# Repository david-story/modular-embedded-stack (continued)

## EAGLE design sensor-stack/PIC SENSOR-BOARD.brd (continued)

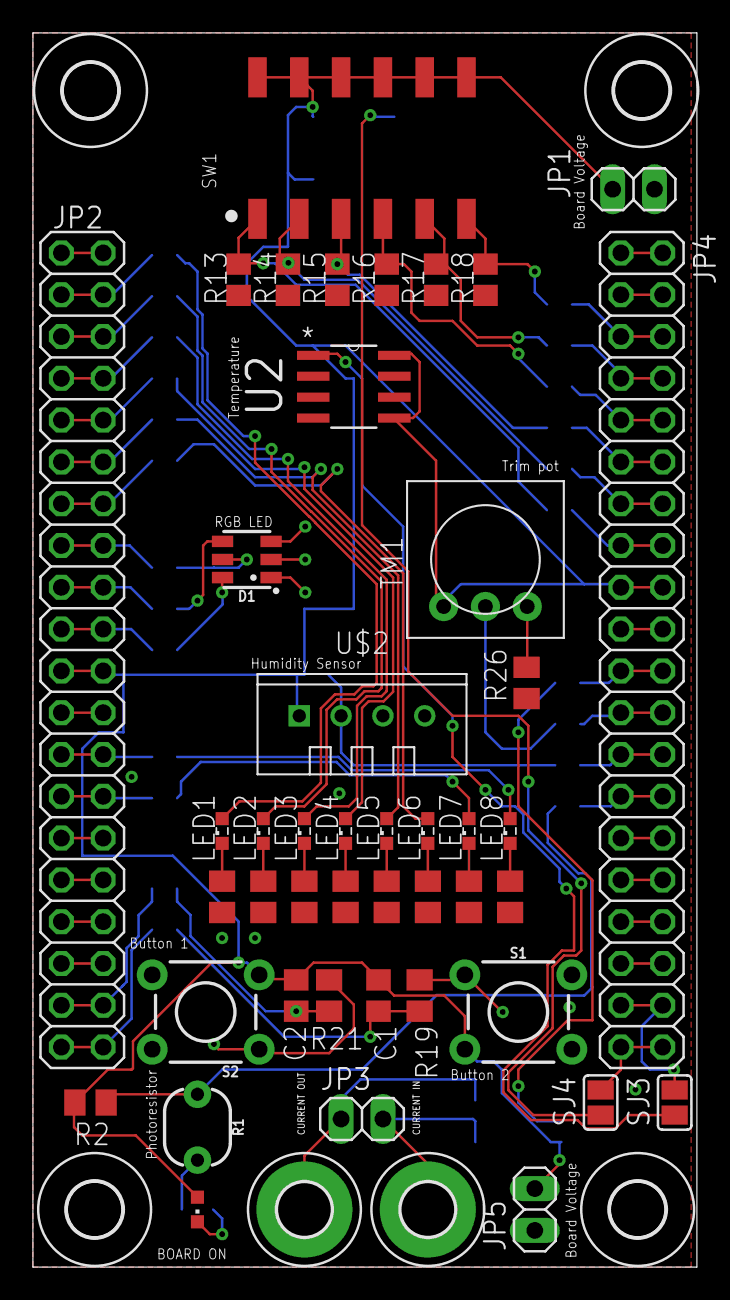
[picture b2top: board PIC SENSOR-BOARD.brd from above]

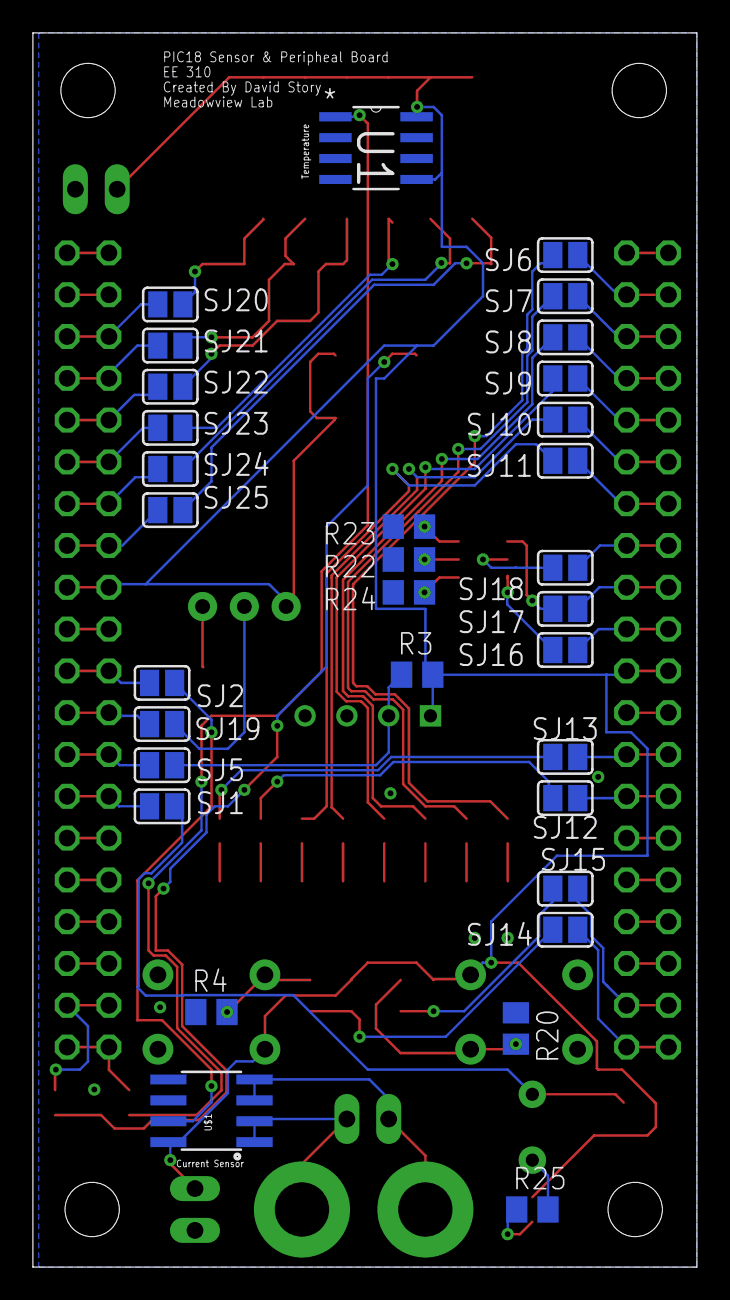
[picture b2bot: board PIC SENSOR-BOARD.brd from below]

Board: 2 copper layers, 40.4 x 75.0 mm, 82 parts (32 on the bottom side), 80 nets.

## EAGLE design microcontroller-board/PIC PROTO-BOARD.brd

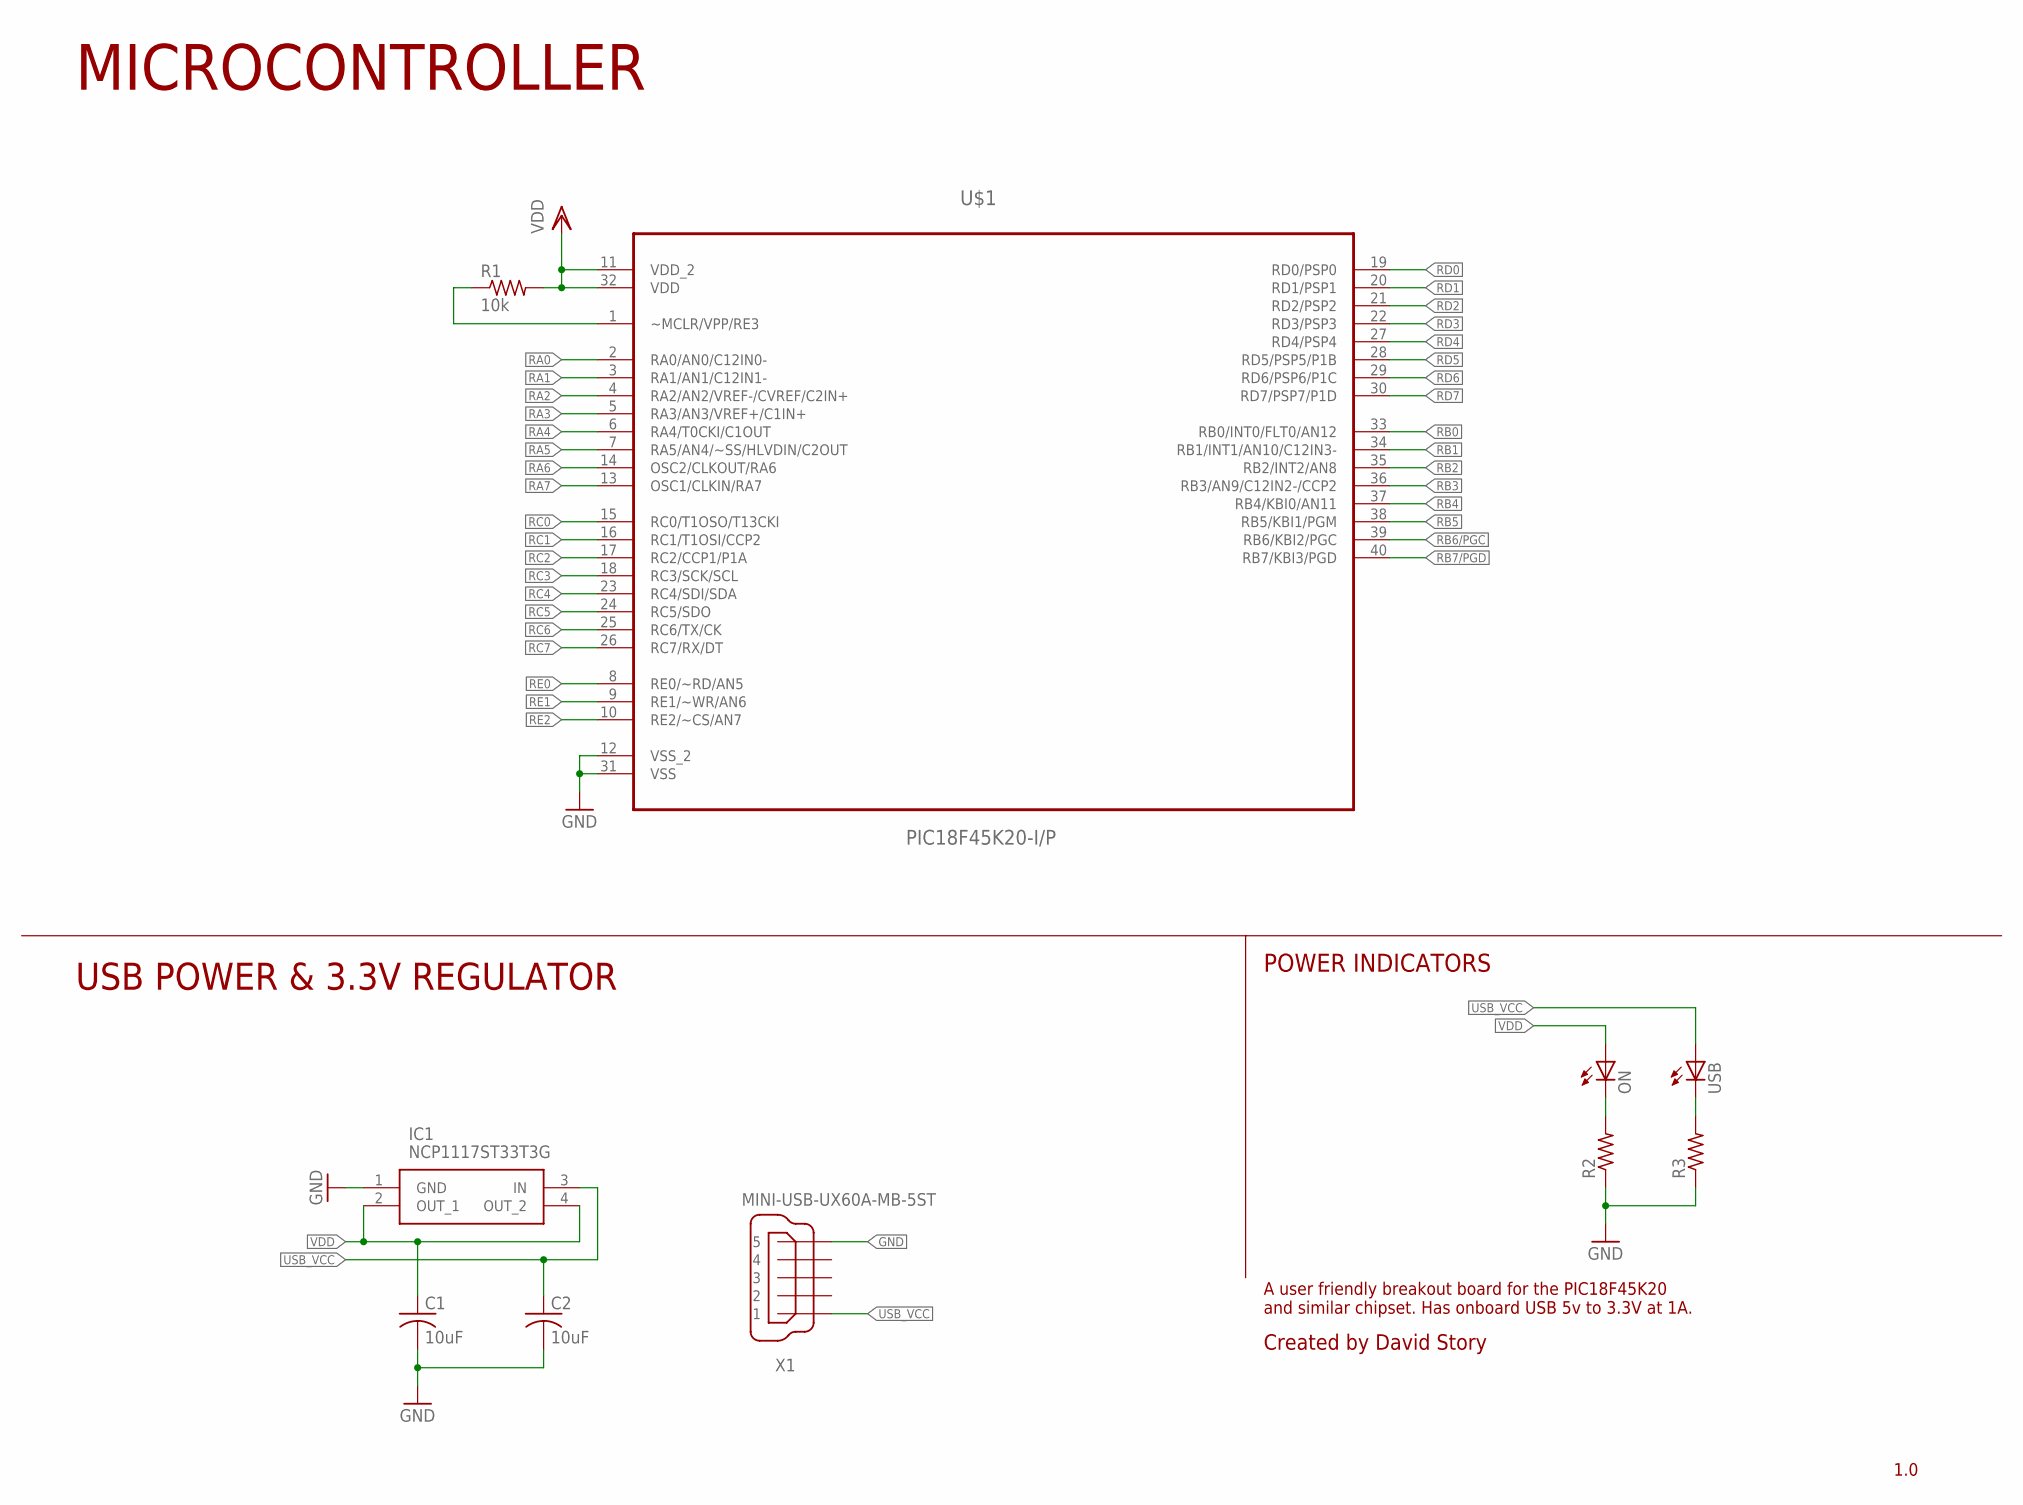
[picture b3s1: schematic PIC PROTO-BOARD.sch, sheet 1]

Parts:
C1, C2: 10uF; C0805
IC1: NCP1117ST33T3G; SOT230P700X180-4N
ON: LEDCHIP-LED0603; CHIP-LED0603
R1: 10k; R0805
R2, R3: R-US_R0603; R0603
U$1: PIC18F45K20-I/P; DIP254P1524X635-40
USB: LEDCHIP-LED0603; CHIP-LED0603
X1: MINI-USB-UX60A-MB-5ST; UX60A-MB-5ST

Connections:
GND: C1.2, C2.2, IC1.1 (GND), R2.1, R3.1, U$1.12 (VSS_2), U$1.31 (VSS), X1.5; also elsewhere on the board
MCLR: R1.1, U$1.1 (~MCLR/VPP/RE3); also elsewhere on the board
ON_CATHODE: ON.C, R2.2
RA0: U$1.2 (RA0/AN0/C12IN0-); also elsewhere on the board
RA1: U$1.3 (RA1/AN1/C12IN1-); also elsewhere on the board
RA2: U$1.4 (RA2/AN2/VREF-/CVREF/C2IN+); also elsewhere on the board
RA3: U$1.5 (RA3/AN3/VREF+/C1IN+); also elsewhere on the board
RA4: U$1.6 (RA4/T0CKI/C1OUT); also elsewhere on the board
RA5: U$1.7 (RA5/AN4/~SS/HLVDIN/C2OUT); also elsewhere on the board
RA6: U$1.14 (OSC2/CLKOUT/RA6); also elsewhere on the board
RA7: U$1.13 (OSC1/CLKIN/RA7); also elsewhere on the board
RB0: U$1.33 (RB0/INT0/FLT0/AN12); also elsewhere on the board
RB1: U$1.34 (RB1/INT1/AN10/C12IN3-); also elsewhere on the board
RB2: U$1.35 (RB2/INT2/AN8); also elsewhere on the board
RB3: U$1.36 (RB3/AN9/C12IN2-/CCP2); also elsewhere on the board
RB4: U$1.37 (RB4/KBI0/AN11); also elsewhere on the board
RB5: U$1.38 (RB5/KBI1/PGM); also elsewhere on the board
RB6/PGC: U$1.39 (RB6/KBI2/PGC); also elsewhere on the board
RB7/PGD: U$1.40 (RB7/KBI3/PGD); also elsewhere on the board
RC0: U$1.15 (RC0/T1OSO/T13CKI); also elsewhere on the board
RC1: U$1.16 (RC1/T1OSI/CCP2); also elsewhere on the board
RC2: U$1.17 (RC2/CCP1/P1A); also elsewhere on the board
RC3: U$1.18 (RC3/SCK/SCL); also elsewhere on the board
RC4: U$1.23 (RC4/SDI/SDA); also elsewhere on the board
RC5: U$1.24 (RC5/SDO); also elsewhere on the board
RC6: U$1.25 (RC6/TX/CK); also elsewhere on the board
RC7: U$1.26 (RC7/RX/DT); also elsewhere on the board
RD0: U$1.19 (RD0/PSP0); also elsewhere on the board
RD1: U$1.20 (RD1/PSP1); also elsewhere on the board
RD2: U$1.21 (RD2/PSP2); also elsewhere on the board
RD3: U$1.22 (RD3/PSP3); also elsewhere on the board
RD4: U$1.27 (RD4/PSP4); also elsewhere on the board
RD5: U$1.28 (RD5/PSP5/P1B); also elsewhere on the board
RD6: U$1.29 (RD6/PSP6/P1C); also elsewhere on the board
RD7: U$1.30 (RD7/PSP7/P1D); also elsewhere on the board
RE0: U$1.8 (RE0/~RD/AN5); also elsewhere on the board
RE1: U$1.9 (RE1/~WR/AN6); also elsewhere on the board
RE2: U$1.10 (RE2/~CS/AN7); also elsewhere on the board
USB_CATHODE: R3.2, USB.C
USB_VCC: C2.1, IC1.3 (IN), USB.A, X1.1
VDD: C1.1, IC1.2 (OUT_1), IC1.4 (OUT_2), ON.A, R1.2, U$1.11 (VDD_2), U$1.32 (VDD); also elsewhere on the board

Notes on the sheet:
Created by David Story
1.0
MICROCONTROLLER
USB POWER & 3.3V REGULATOR
POWER INDICATORS
A user friendly breakout board for the PIC18F45K20 and similar chipset. Has onboard USB 5v to 3.3V at 1A.

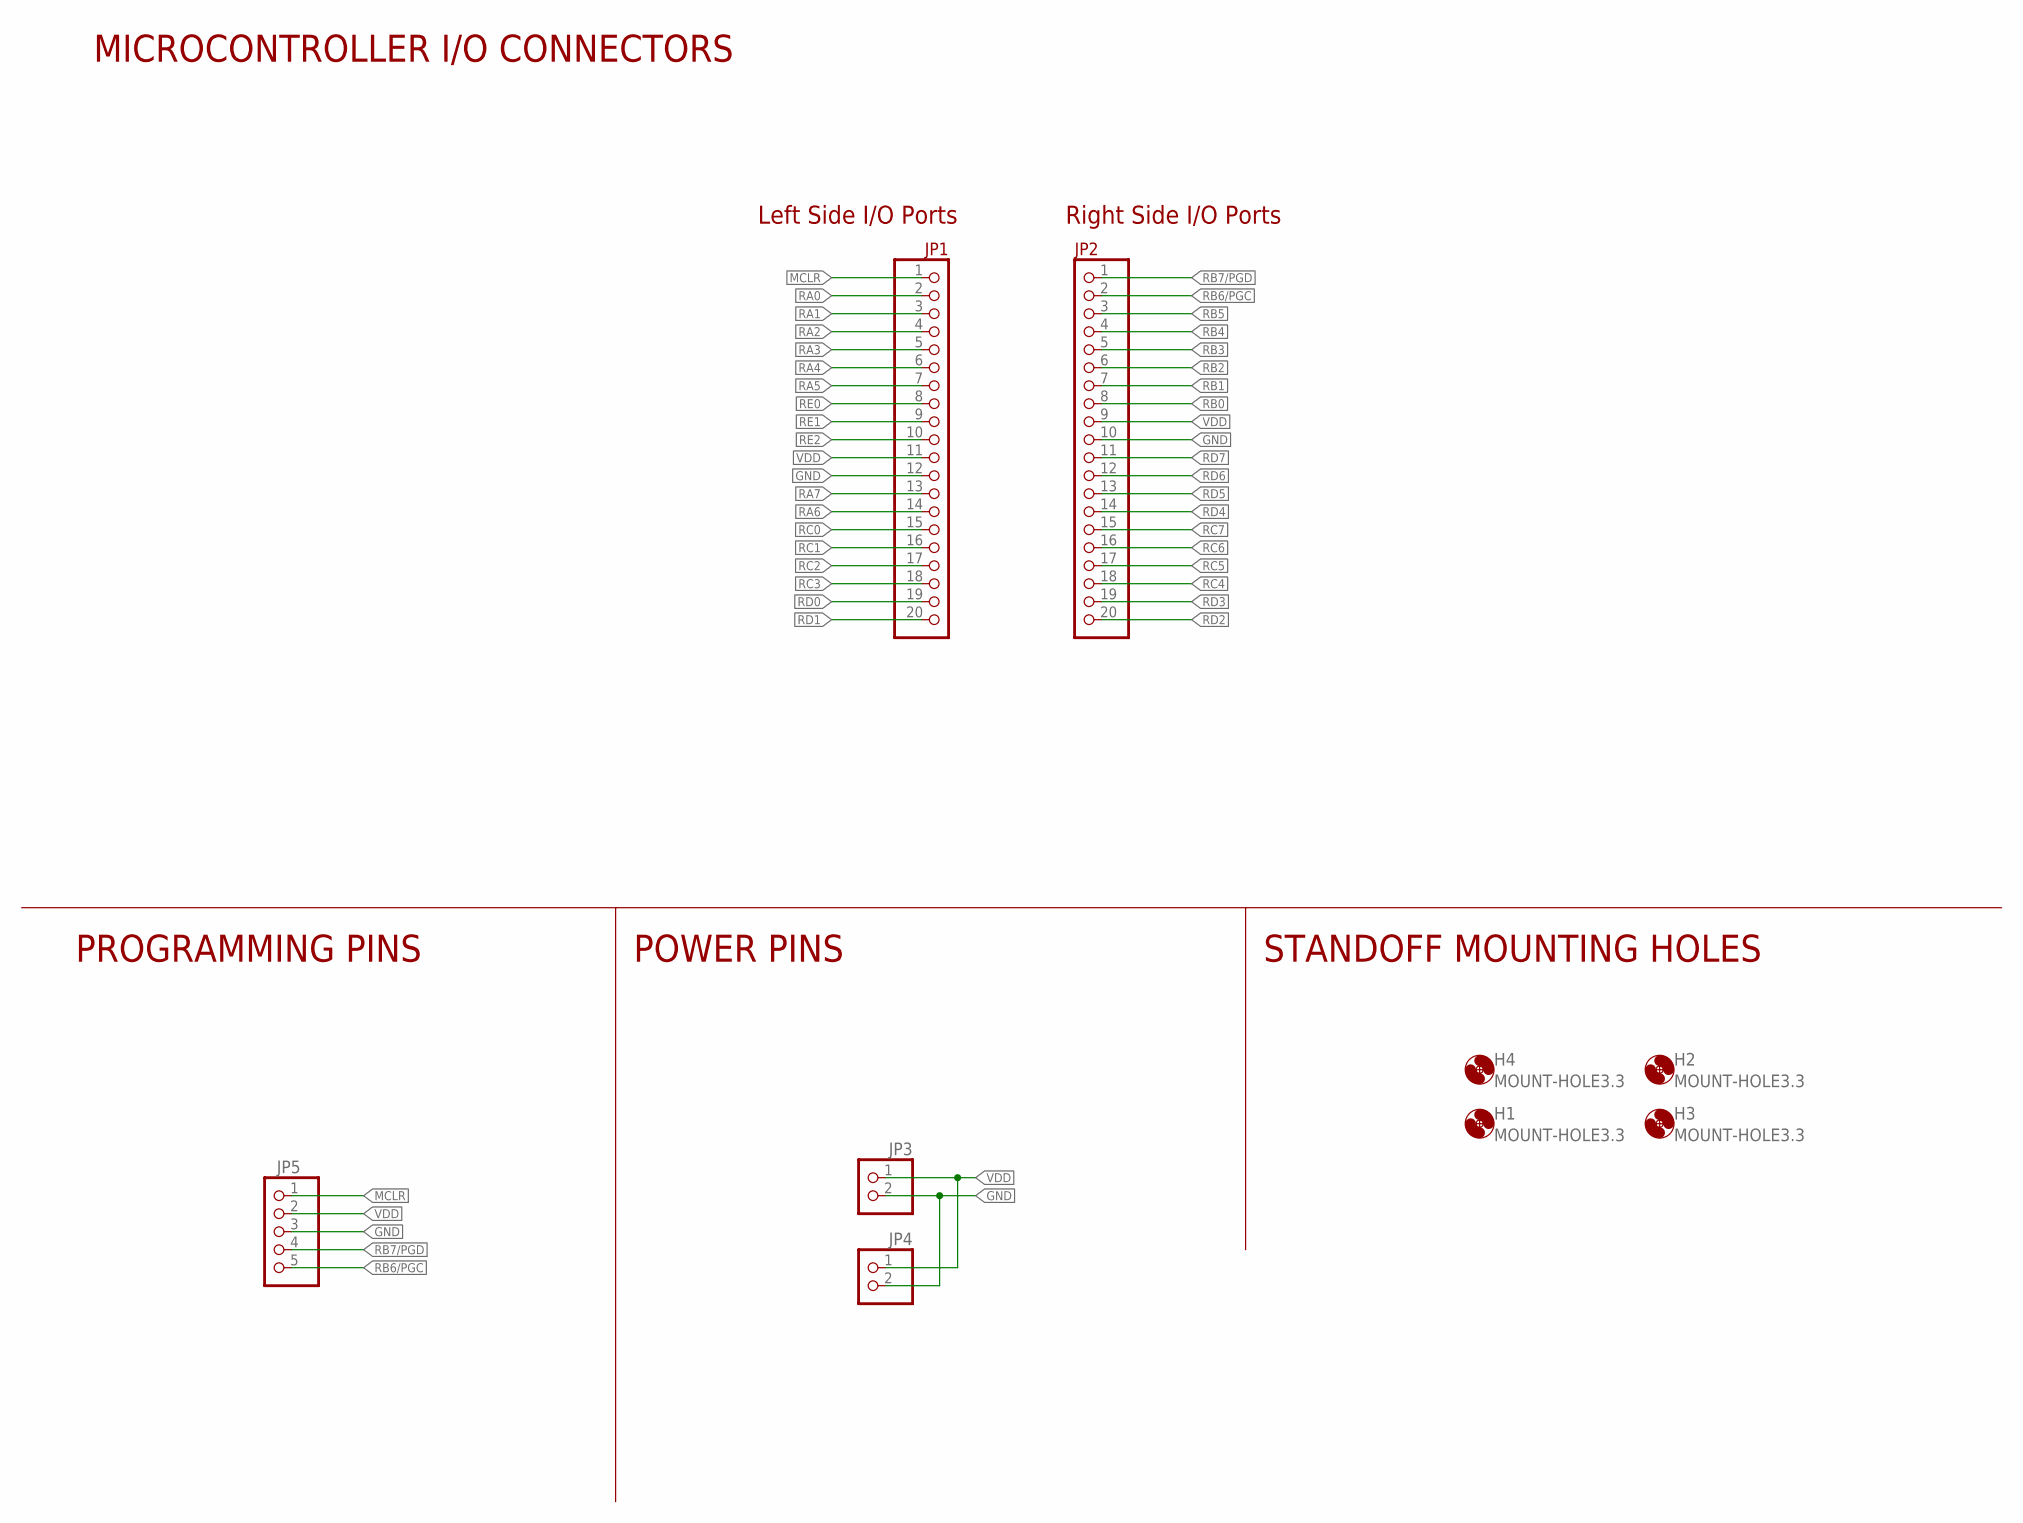
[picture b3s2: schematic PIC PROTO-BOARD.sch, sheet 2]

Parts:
H1, H2, H3, H4: MOUNT-HOLE3.3; 3,3
JP1, JP2: PINHD-1X20; 1X20
JP3, JP4: PINHD-1X2; 1X02
JP5: PINHD-1X5; 1X05

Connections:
GND: JP1.12, JP2.10, JP3.2, JP4.2, JP5.3; also elsewhere on the board
MCLR: JP1.1, JP5.1; also elsewhere on the board
RA0: JP1.2; also elsewhere on the board
RA1: JP1.3; also elsewhere on the board
RA2: JP1.4; also elsewhere on the board
RA3: JP1.5; also elsewhere on the board
RA4: JP1.6; also elsewhere on the board
RA5: JP1.7; also elsewhere on the board
RA6: JP1.14; also elsewhere on the board
RA7: JP1.13; also elsewhere on the board
RB0: JP2.8; also elsewhere on the board
RB1: JP2.7; also elsewhere on the board
RB2: JP2.6; also elsewhere on the board
RB3: JP2.5; also elsewhere on the board
RB4: JP2.4; also elsewhere on the board
RB5: JP2.3; also elsewhere on the board
RB6/PGC: JP2.2, JP5.5; also elsewhere on the board
RB7/PGD: JP2.1, JP5.4; also elsewhere on the board
RC0: JP1.15; also elsewhere on the board
RC1: JP1.16; also elsewhere on the board
RC2: JP1.17; also elsewhere on the board
RC3: JP1.18; also elsewhere on the board
RC4: JP2.18; also elsewhere on the board
RC5: JP2.17; also elsewhere on the board
RC6: JP2.16; also elsewhere on the board
RC7: JP2.15; also elsewhere on the board
RD0: JP1.19; also elsewhere on the board
RD1: JP1.20; also elsewhere on the board
RD2: JP2.20; also elsewhere on the board
RD3: JP2.19; also elsewhere on the board
RD4: JP2.14; also elsewhere on the board
RD5: JP2.13; also elsewhere on the board
RD6: JP2.12; also elsewhere on the board
RD7: JP2.11; also elsewhere on the board
RE0: JP1.8; also elsewhere on the board
RE1: JP1.9; also elsewhere on the board
RE2: JP1.10; also elsewhere on the board
VDD: JP1.11, JP2.9, JP3.1, JP4.1, JP5.2; also elsewhere on the board

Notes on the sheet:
Left Side I/O Ports
Right Side I/O Ports
PROGRAMMING PINS
POWER PINS
STANDOFF MOUNTING HOLES
MICROCONTROLLER I/O CONNECTORS

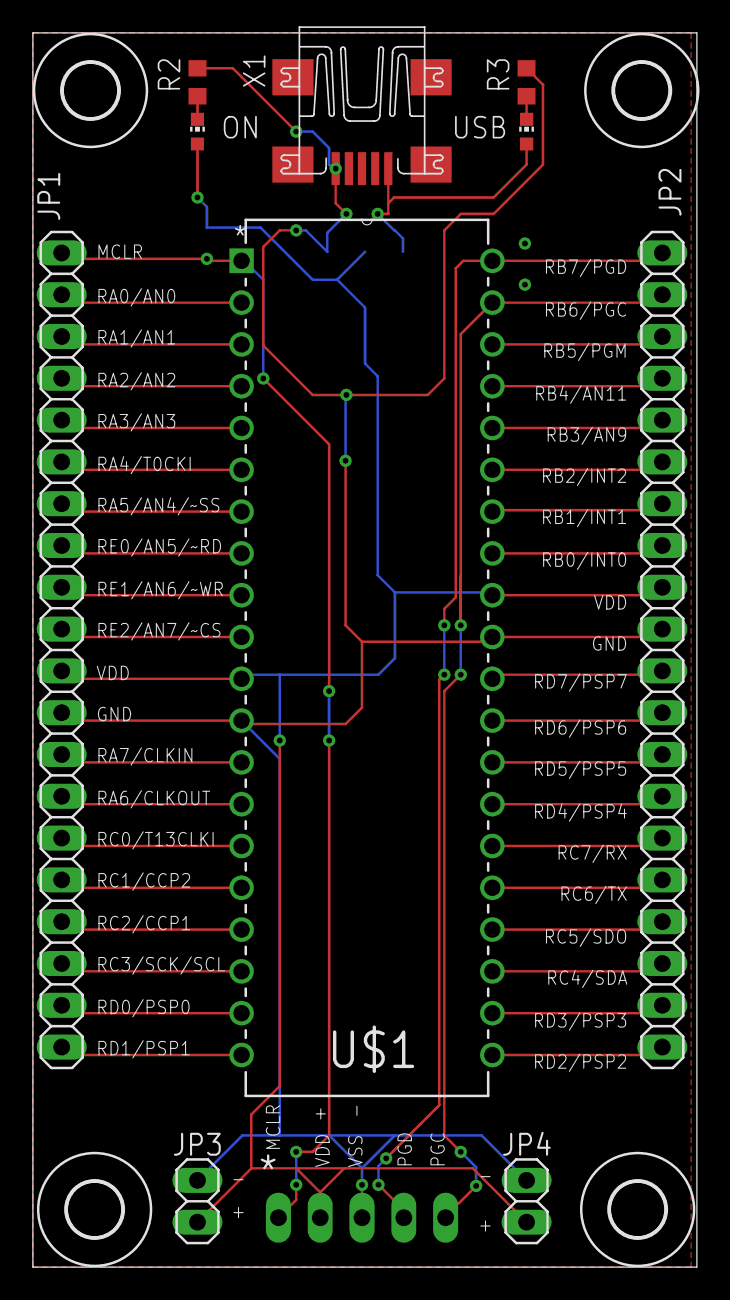
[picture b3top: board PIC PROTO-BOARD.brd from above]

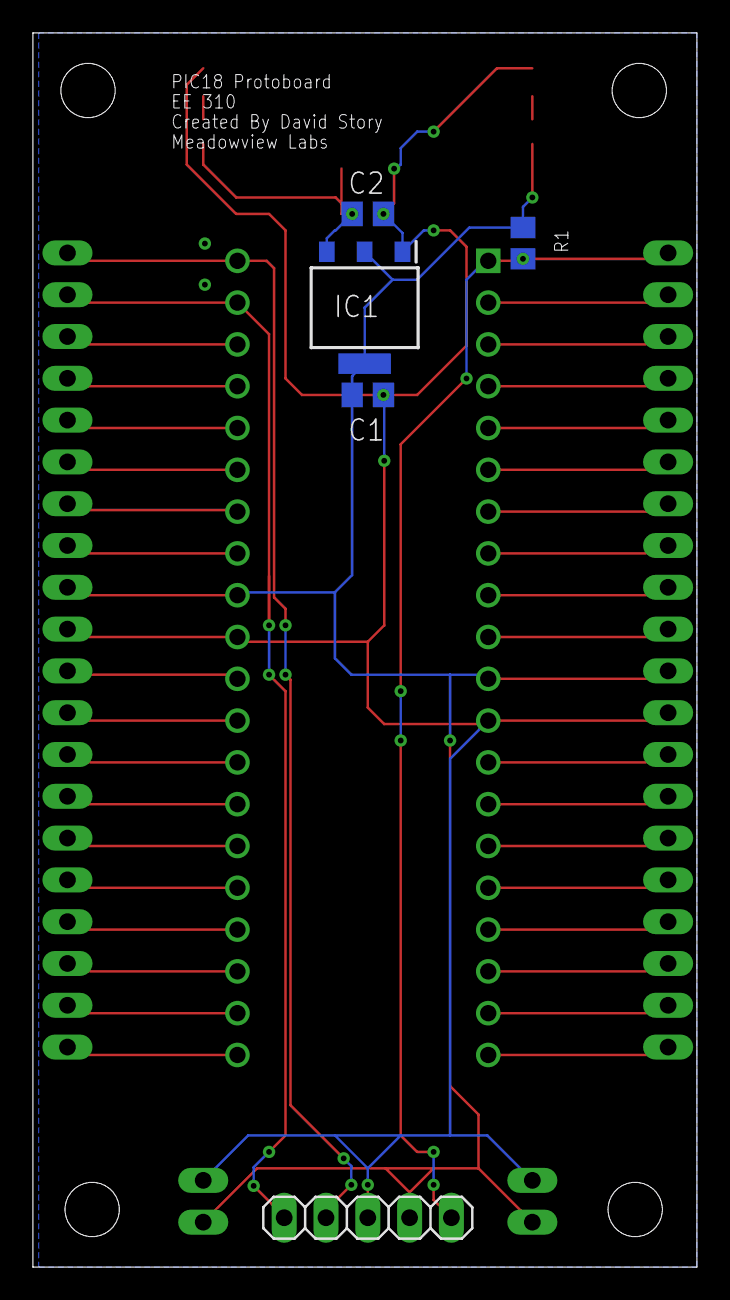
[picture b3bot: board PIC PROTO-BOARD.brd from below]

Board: 2 copper layers, 40.4 x 75.0 mm, 19 parts (5 on the bottom side), 41 nets.

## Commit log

2019-02-07 Added some board files
2019-02-10 Added Sensor Board
2019-03-03 Added SMD verison of microcontroller board
2019-03-23 Added Project File
